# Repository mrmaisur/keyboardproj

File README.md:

# keyboardproj
first attempt at making a pcb, keyboard

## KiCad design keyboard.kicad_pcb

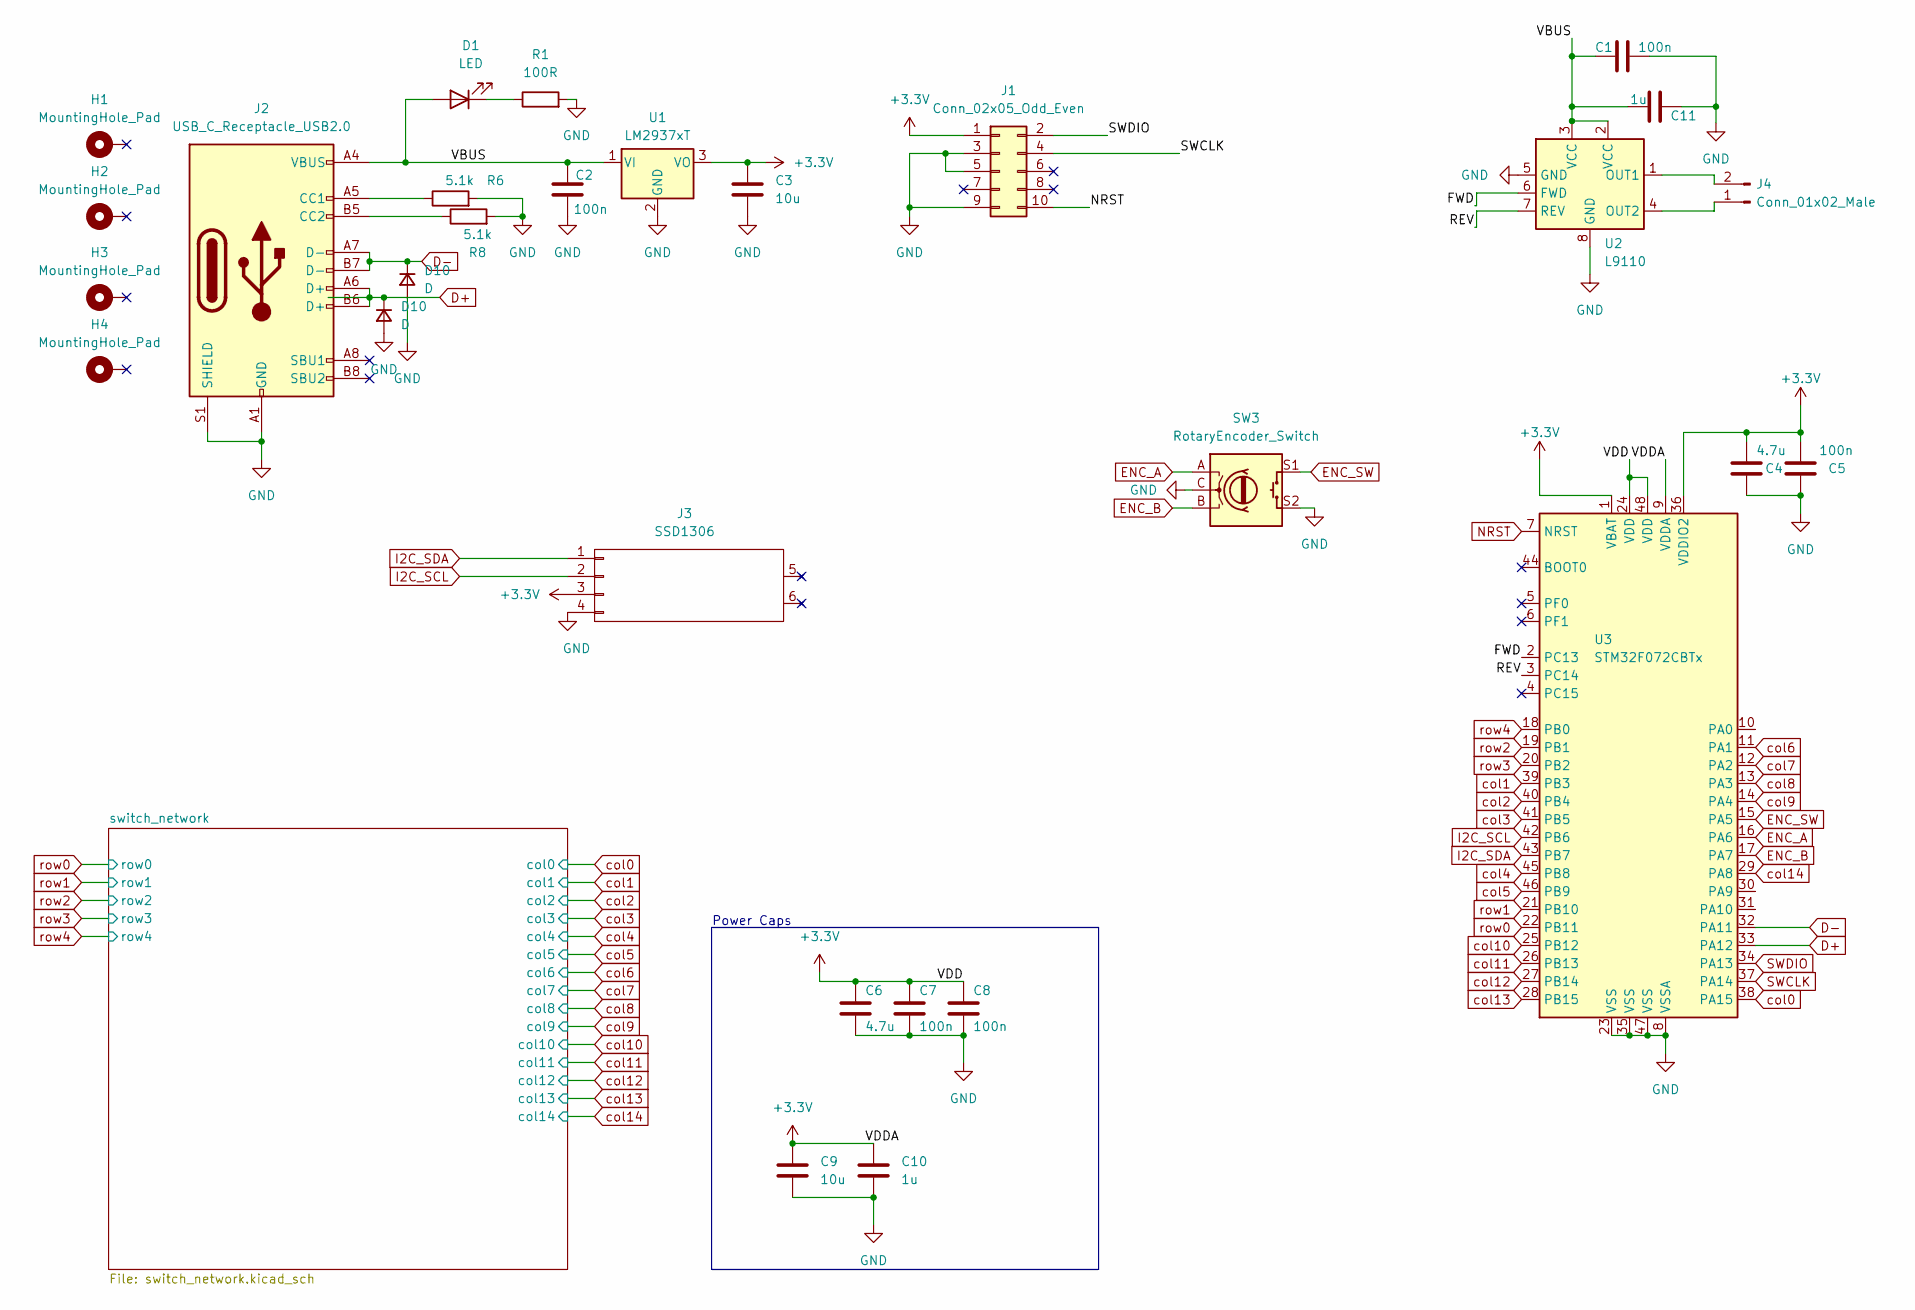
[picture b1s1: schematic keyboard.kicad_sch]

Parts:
C1, C2: 100n; C_0805_2012Metric
C3, C9: 10u; C_0805_2012Metric
C4, C6: 4.7u; C_0805_2012Metric
C5, C7, C8: 100n; C_0603_1608Metric
C10, C11: 1u; C_0805_2012Metric
D1: LED; LED_D3.0mm_Clear
D10: D; D_DO-35_SOD27_P5.08mm_Horizontal
H1, H2, H3, H4: MountingHole_Pad; MountingHole_3.2mm_M3_Pad
J1: Conn_02x05_Odd_Even; 322010010000
J2: USB_C_Receptacle_USB2.0; USB_C_Receptacle_G-Switch_GT-USB-7010ASV
J3: SSD1306
J4: Conn_01x02_Male; PinHeader_1x02_P2.54mm_Vertical
R1: 100R; R_Axial_DIN0207_L6.3mm_D2.5mm_P7.62mm_Horizontal
R6, R8: 5.1k; R_Axial_DIN0207_L6.3mm_D2.5mm_P7.62mm_Horizontal
SW3: RotaryEncoder_Switch; RotaryEncoder_Alps_EC11E-Switch_Vertical_H20mm
U1: LM2937xT; TO-220-3_Horizontal_TabDown
U2: L9110; DIP-8_W7.62mm
U3: STM32F072CBTx; LQFP-48_7x7mm_P0.5mm

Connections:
+3.3V: C3.1, C4.1, C5.1, C6.1, C7.1, C8.1, C9.1, C10.1, J1.1, J3.3 (VCC), U1.3 (VO), U3.1 (VBAT), U3.9 (VDDA), U3.24 (VDD), U3.36 (VDDIO2), U3.48 (VDD)
/FWD: U2.6 (FWD), U3.2 (PC13)
/REV: U2.7 (REV), U3.3 (PC14)
/VBUS: C1.1, C2.1, C11.1, D1.2 (A), J2.A4 (VBUS), J2.A9 (VBUS), J2.B4 (VBUS), J2.B9 (VBUS), U1.1 (VI), U2.2 (VCC), U2.3 (VCC)
ENC_A: SW3.A, U3.16 (PA6)
ENC_B: SW3.B, U3.17 (PA7)
ENC_SW: SW3.S1, U3.15 (PA5)
I2C_SCL: J3.2 (SCL), U3.42 (PB6)
I2C_SDA: J3.1 (SDA), U3.43 (PB7)
NRST: J1.10, U3.7 (NRST)
unnamed: D1.1 (K), R1.1
unnamed: J2.A5 (CC1), R6.1
unnamed: J2.B5 (CC2), R8.1
unnamed: J4.1, U2.4 (OUT2)
unnamed: J4.2, U2.1 (OUT1)
SWCLK: J1.4, U3.37 (PA14)
SWDIO: J1.2, U3.34 (PA13)
col0: U3.38 (PA15); also elsewhere on the board
col1: U3.39 (PB3); also elsewhere on the board
col2: U3.40 (PB4); also elsewhere on the board
col3: U3.41 (PB5); also elsewhere on the board
col4: U3.45 (PB8); also elsewhere on the board
col5: U3.46 (PB9); also elsewhere on the board
col6: U3.11 (PA1); also elsewhere on the board
col7: U3.12 (PA2); also elsewhere on the board
col8: U3.13 (PA3); also elsewhere on the board
col9: U3.14 (PA4); also elsewhere on the board
col10: U3.25 (PB12); also elsewhere on the board
col11: U3.26 (PB13); also elsewhere on the board
col12: U3.27 (PB14); also elsewhere on the board
col13: U3.28 (PB15); also elsewhere on the board
col14: U3.29 (PA8); also elsewhere on the board
row1: U3.21 (PB10); also elsewhere on the board
row2: U3.19 (PB1); also elsewhere on the board
row3: U3.20 (PB2); also elsewhere on the board
row4: U3.18 (PB0); also elsewhere on the board

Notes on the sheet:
Power Caps

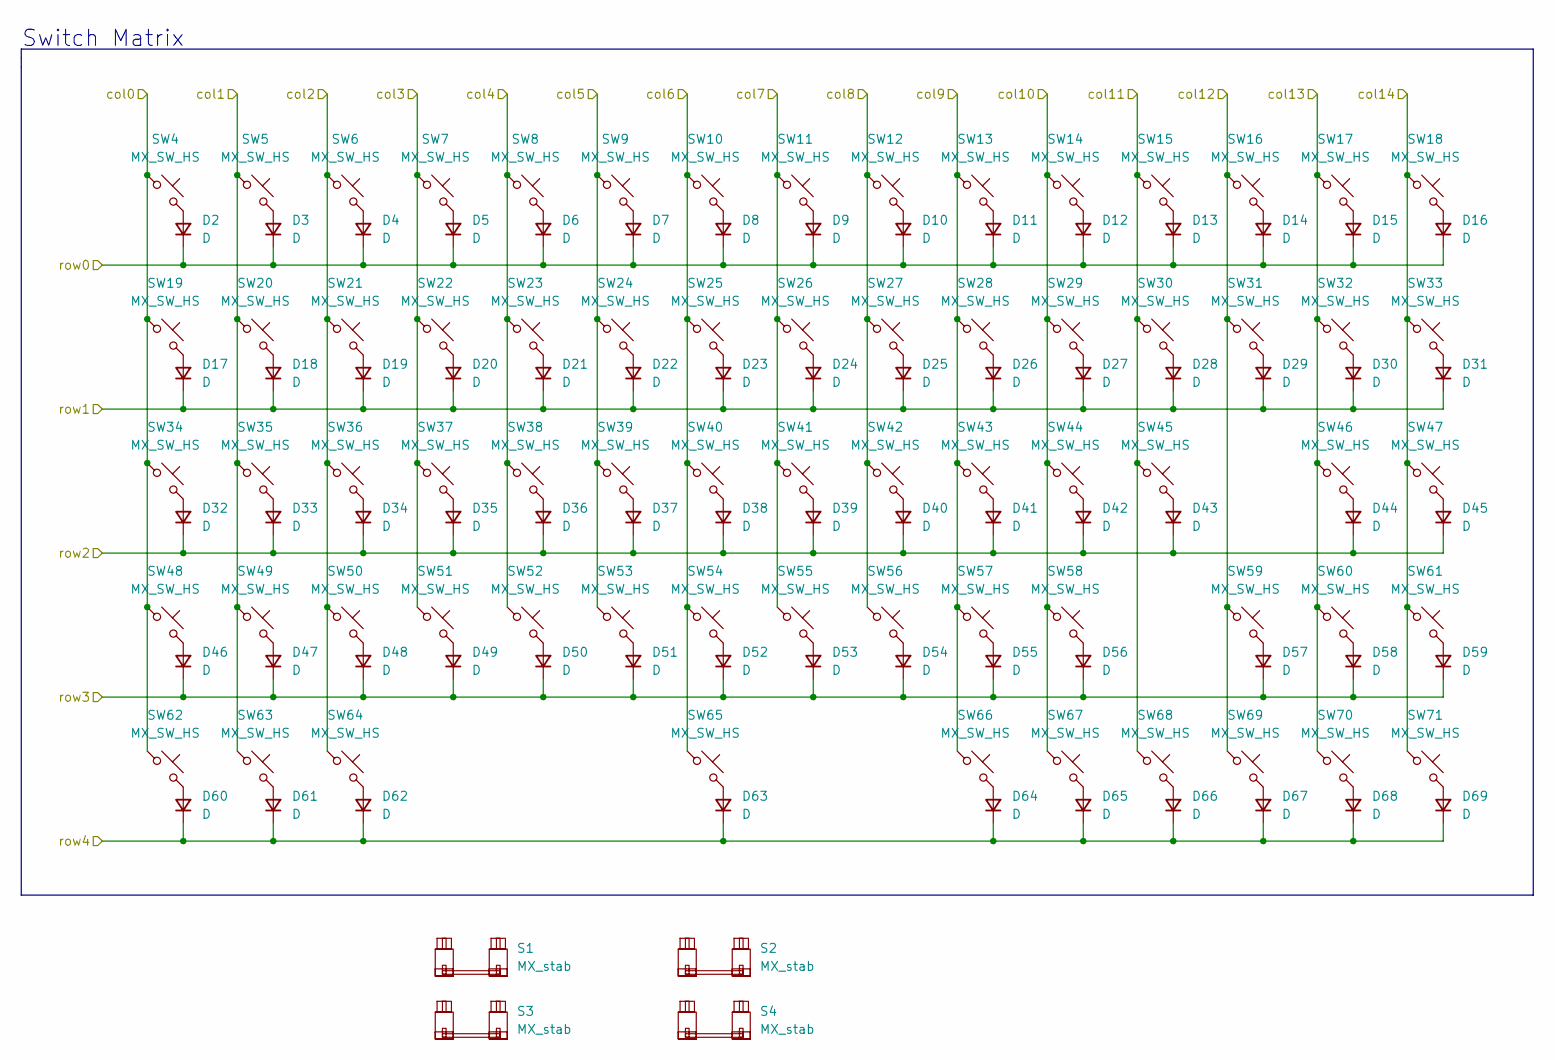
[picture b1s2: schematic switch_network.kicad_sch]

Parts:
D2, D3, D4, D5, D6, D7, D8, D9, D10, D11, D12, D13, D14, D15, D16, D17, D18, D19, D20, D21, D22, D23, D24, D25, D26, D27, D28, D29, D30, D31, D32, D33, D34, D35, D36, D37, D38, D39, D40, D41, D42, D43, D44, D45, D46, D47, D48, D49, D50, D51, D52, D53, D54, D55, D56, D57, D58, D59, D60, D61, D62, D63, D64, D65, D66, D67, D68, D69: D; D_DO-35_SOD27_P5.08mm_Horizontal
S1, S3: MX_stab; STAB_MX_2.25u
S2: MX_stab; STAB_MX_6.25u
S4: MX_stab; STAB_MX_2u
SW4, SW5, SW6, SW7, SW8, SW9, SW10, SW11, SW12, SW13, SW14, SW15, SW16, SW17, SW18, SW20, SW21, SW22, SW23, SW24, SW25, SW26, SW27, SW28, SW29, SW30, SW31, SW33, SW35, SW36, SW37, SW38, SW39, SW40, SW41, SW42, SW43, SW44, SW45, SW46, SW47, SW48, SW49, SW50, SW51, SW52, SW53, SW54, SW55, SW56, SW57, SW58, SW60, SW61, SW65, SW66, SW67, SW68, SW69, SW70, SW71: MX_SW_HS; SW_MX_1u
SW19, SW32: MX_SW_HS; SW_MX_1.5u
SW34, SW59: MX_SW_HS; SW_MX_1.75u
SW62, SW63, SW64: MX_SW_HS; SW_MX_1.25u

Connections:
unnamed: D2.2 (A), SW4.2
unnamed: D3.2 (A), SW5.2
unnamed: D4.2 (A), SW6.2
unnamed: D5.2 (A), SW7.2
unnamed: D6.2 (A), SW8.2
unnamed: D7.2 (A), SW9.2
unnamed: D8.2 (A), SW10.2
unnamed: D9.2 (A), SW11.2
unnamed: D11.2 (A), SW13.2
unnamed: D12.2 (A), SW14.2
unnamed: D13.2 (A), SW15.2
unnamed: D14.2 (A), SW16.2
unnamed: D15.2 (A), SW17.2
unnamed: D16.2 (A), SW18.2
unnamed: D17.2 (A), SW19.2
unnamed: D18.2 (A), SW20.2
unnamed: D19.2 (A), SW21.2
unnamed: D20.2 (A), SW22.2
unnamed: D21.2 (A), SW23.2
unnamed: D22.2 (A), SW24.2
unnamed: D23.2 (A), SW25.2
unnamed: D24.2 (A), SW26.2
unnamed: D25.2 (A), SW27.2
unnamed: D26.2 (A), SW28.2
unnamed: D27.2 (A), SW29.2
unnamed: D28.2 (A), SW30.2
unnamed: D29.2 (A), SW31.2
unnamed: D30.2 (A), SW32.2
unnamed: D31.2 (A), SW33.2
unnamed: D32.2 (A), SW34.2
unnamed: D33.2 (A), SW35.2
unnamed: D34.2 (A), SW36.2
unnamed: D35.2 (A), SW37.2
unnamed: D36.2 (A), SW38.2
unnamed: D37.2 (A), SW39.2
unnamed: D38.2 (A), SW40.2
unnamed: D39.2 (A), SW41.2
unnamed: D40.2 (A), SW42.2
unnamed: D41.2 (A), SW43.2
unnamed: D42.2 (A), SW44.2
unnamed: D43.2 (A), SW45.2
unnamed: D44.2 (A), SW46.2
unnamed: D45.2 (A), SW47.2
unnamed: D46.2 (A), SW48.2
unnamed: D47.2 (A), SW49.2
unnamed: D48.2 (A), SW50.2
unnamed: D49.2 (A), SW51.2
unnamed: D50.2 (A), SW52.2
unnamed: D51.2 (A), SW53.2
unnamed: D52.2 (A), SW54.2
unnamed: D53.2 (A), SW55.2
unnamed: D54.2 (A), SW56.2
unnamed: D55.2 (A), SW57.2
unnamed: D56.2 (A), SW58.2
unnamed: D57.2 (A), SW59.2
unnamed: D58.2 (A), SW60.2
unnamed: D59.2 (A), SW61.2
unnamed: D60.2 (A), SW62.2
unnamed: D61.2 (A), SW63.2
unnamed: D62.2 (A), SW64.2
unnamed: D63.2 (A), SW65.2
unnamed: D64.2 (A), SW66.2
unnamed: D65.2 (A), SW67.2
unnamed: D66.2 (A), SW68.2
unnamed: D67.2 (A), SW69.2
unnamed: D68.2 (A), SW70.2
unnamed: D69.2 (A), SW71.2
col0: SW4.1, SW19.1, SW34.1, SW48.1, SW62.1; also elsewhere on the board
col1: SW5.1, SW20.1, SW35.1, SW49.1, SW63.1; also elsewhere on the board
col2: SW6.1, SW21.1, SW36.1, SW50.1, SW64.1; also elsewhere on the board
col3: SW7.1, SW22.1, SW37.1, SW51.1; also elsewhere on the board
col4: SW8.1, SW23.1, SW38.1, SW52.1; also elsewhere on the board
col5: SW9.1, SW24.1, SW39.1, SW53.1; also elsewhere on the board
col6: SW10.1, SW25.1, SW40.1, SW54.1, SW65.1; also elsewhere on the board
col7: SW11.1, SW26.1, SW41.1, SW55.1; also elsewhere on the board
col8: SW12.1, SW27.1, SW42.1, SW56.1; also elsewhere on the board
col9: SW13.1, SW28.1, SW43.1, SW57.1, SW66.1; also elsewhere on the board
col10: SW14.1, SW29.1, SW44.1, SW58.1, SW67.1; also elsewhere on the board
col11: SW15.1, SW30.1, SW45.1, SW68.1; also elsewhere on the board
col12: SW16.1, SW31.1, SW59.1, SW69.1; also elsewhere on the board
col13: SW17.1, SW32.1, SW46.1, SW60.1, SW70.1; also elsewhere on the board
col14: SW18.1, SW33.1, SW47.1, SW61.1, SW71.1; also elsewhere on the board
row1: D17.1 (K), D18.1 (K), D19.1 (K), D20.1 (K), D21.1 (K), D22.1 (K), D23.1 (K), D24.1 (K), D25.1 (K), D26.1 (K), D27.1 (K), D28.1 (K), D29.1 (K), D30.1 (K), D31.1 (K); also elsewhere on the board
row2: D32.1 (K), D33.1 (K), D34.1 (K), D35.1 (K), D36.1 (K), D37.1 (K), D38.1 (K), D39.1 (K), D40.1 (K), D41.1 (K), D42.1 (K), D43.1 (K), D44.1 (K), D45.1 (K); also elsewhere on the board
row3: D46.1 (K), D47.1 (K), D48.1 (K), D49.1 (K), D50.1 (K), D51.1 (K), D52.1 (K), D53.1 (K), D54.1 (K), D55.1 (K), D56.1 (K), D57.1 (K), D58.1 (K), D59.1 (K); also elsewhere on the board
row4: D60.1 (K), D61.1 (K), D62.1 (K), D63.1 (K), D64.1 (K), D65.1 (K), D66.1 (K), D67.1 (K), D68.1 (K), D69.1 (K); also elsewhere on the board

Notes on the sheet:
Switch Matrix

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
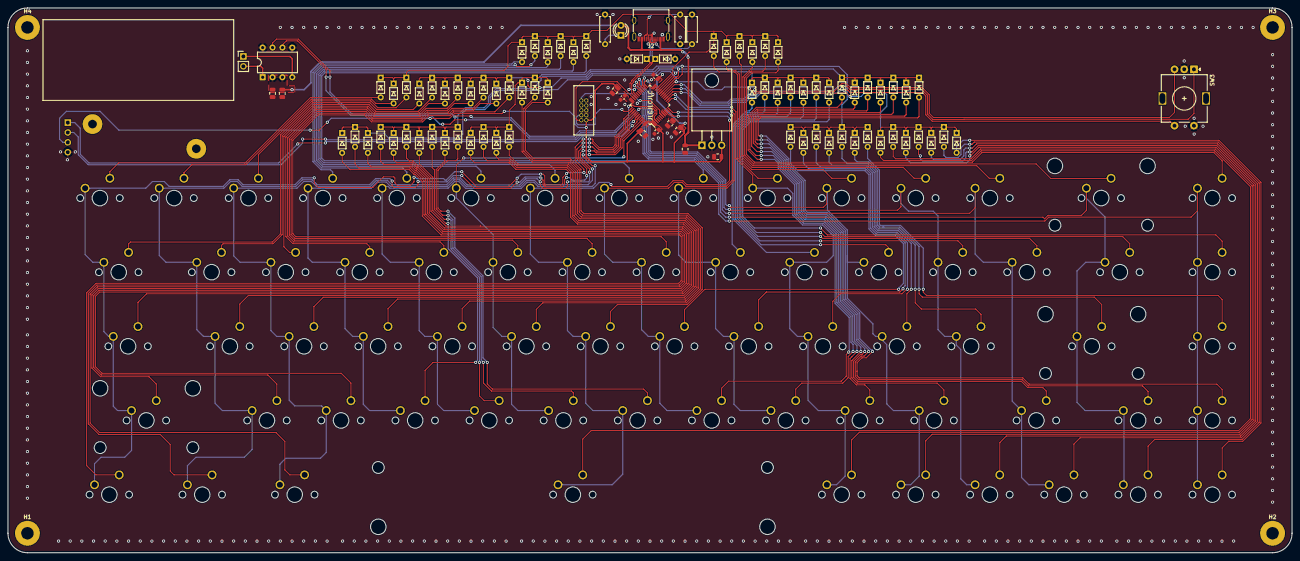
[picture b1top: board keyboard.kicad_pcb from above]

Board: 2 copper layers, 330.0 x 140.0 mm, 169 parts (0 on the bottom side), 108 nets.

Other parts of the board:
D70, D71: D; D_DO-35_SOD27_P5.08mm_Horizontal

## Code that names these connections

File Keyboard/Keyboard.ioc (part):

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Mcu.Name=STM32F072C(8-B)Tx
Mcu.Package=LQFP48
Mcu.UserName=STM32F072CBTx
PA1.Signal=GPIO_Output
PA11.Mode=Device
PA11.Signal=USB_DM
PA12.Mode=Device
PA12.Signal=USB_DP
PA13.Mode=Serial_Wire
PA13.Signal=SYS_SWDIO
PA14.Mode=Serial_Wire
PA14.Signal=SYS_SWCLK
PA15.Signal=GPIO_Output
PA2.Signal=GPIO_Output
PA3.Signal=GPIO_Output
PA4.Signal=GPIO_Output
PA5.Signal=GPIO_Output
PA6.Mode=IN6
PA6.Signal=ADC_IN6
PA7.Mode=IN7
PA7.Signal=ADC_IN7
PA8.Signal=GPIO_Output
PB0.GPIOParameters=GPIO_PuPd,GPIO_Mode
PB0.GPIO_Mode=GPIO_MODE_INPUT
PB0.GPIO_PuPd=GPIO_PULLDOWN
PB0.Signal=GPIO_Input
PB1.GPIOParameters=GPIO_PuPd,GPIO_Mode
PB1.GPIO_Mode=GPIO_MODE_INPUT
PB1.GPIO_PuPd=GPIO_PULLDOWN
PB1.Signal=GPIO_Input
PB10.GPIOParameters=GPIO_PuPd,GPIO_Mode
PB10.GPIO_Mode=GPIO_MODE_INPUT
PB10.GPIO_PuPd=GPIO_PULLDOWN
PB10.Signal=GPIO_Input
PB11.GPIOParameters=GPIO_PuPd,GPIO_Mode
PB11.GPIO_Mode=GPIO_MODE_INPUT
PB11.GPIO_PuPd=GPIO_PULLDOWN
PB11.Signal=GPIO_Input
PB12.Signal=GPIO_Output
PB13.Signal=GPIO_Output
PB14.Signal=GPIO_Output
PB15.Signal=GPIO_Output
PB2.GPIOParameters=GPIO_PuPd,GPIO_Mode
PB2.GPIO_Mode=GPIO_MODE_INPUT
PB2.GPIO_PuPd=GPIO_PULLDOWN
PB2.Signal=GPIO_Input
PB3.Signal=GPIO_Output
PB4.Signal=GPIO_Output
PB5.Signal=GPIO_Output
PB6.Mode=I2C
PB6.Signal=I2C1_SCL
PB7.Mode=I2C
PB7.Signal=I2C1_SDA
PB8.Signal=GPIO_Output
PB9.Signal=GPIO_Output
RCC.SYSCLKFreq_VALUE=48000000
RCC.SYSCLKSource=RCC_SYSCLKSOURCE_HSI48
board=custom

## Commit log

2023-06-27 Added all current progress
2023-06-28 changed layout, started routing
2023-06-28 more wiring done
2023-06-29 nuked traces, start again
2023-07-01 added more traces
2023-07-03 more traces done
2024-09-15 code?
2024-09-15 code
2024-09-27 what
2024-11-05 working without volume ctrl
